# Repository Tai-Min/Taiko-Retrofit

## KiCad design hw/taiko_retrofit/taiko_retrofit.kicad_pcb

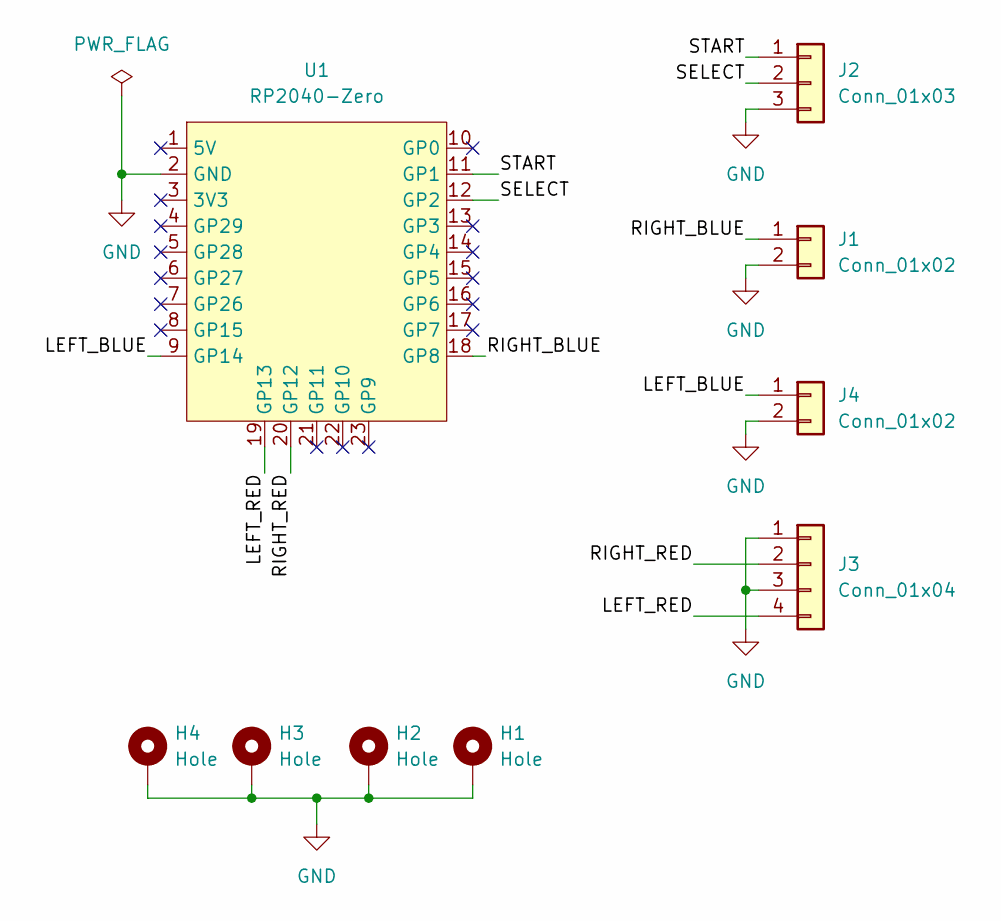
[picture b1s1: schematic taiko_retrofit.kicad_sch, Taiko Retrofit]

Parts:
H1, H2, H3, H4: Hole; MountingHole_3.2mm_M3_Pad_Via
J1, J4: Conn_01x02; Taiko2Pins
J2: Conn_01x03; JST_XH_B3B-XH-A_1x03_P2.50mm_Vertical
J3: Conn_01x04; Taiko4Pins
U1: RP2040-Zero; RP2040 Zero

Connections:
/LEFT_BLUE: J4.1, U1.9 (GP14)
/LEFT_RED: J3.4, U1.19 (GP13)
/RIGHT_BLUE: J1.1, U1.18 (GP8)
/RIGHT_RED: J3.2, U1.20 (GP12)
/SELECT: J2.2, U1.12 (GP2)
/START: J2.1, U1.11 (GP1)
GND: H1.1, H2.1, H3.1, H4.1, J1.2, J2.3, J3.1, J3.3, J4.2, U1.2 (GND)

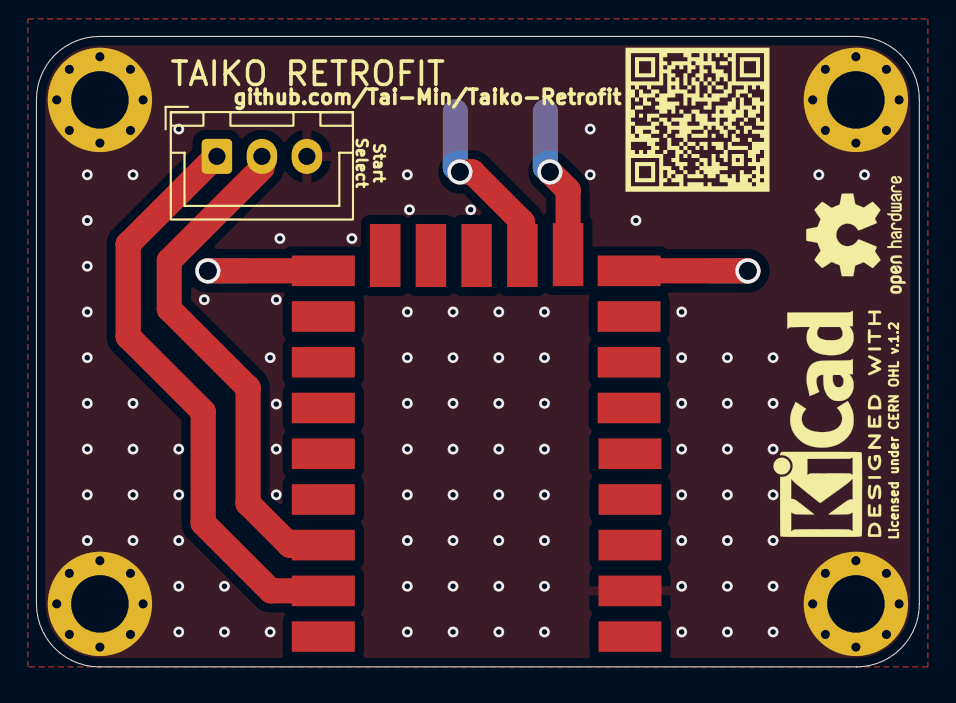
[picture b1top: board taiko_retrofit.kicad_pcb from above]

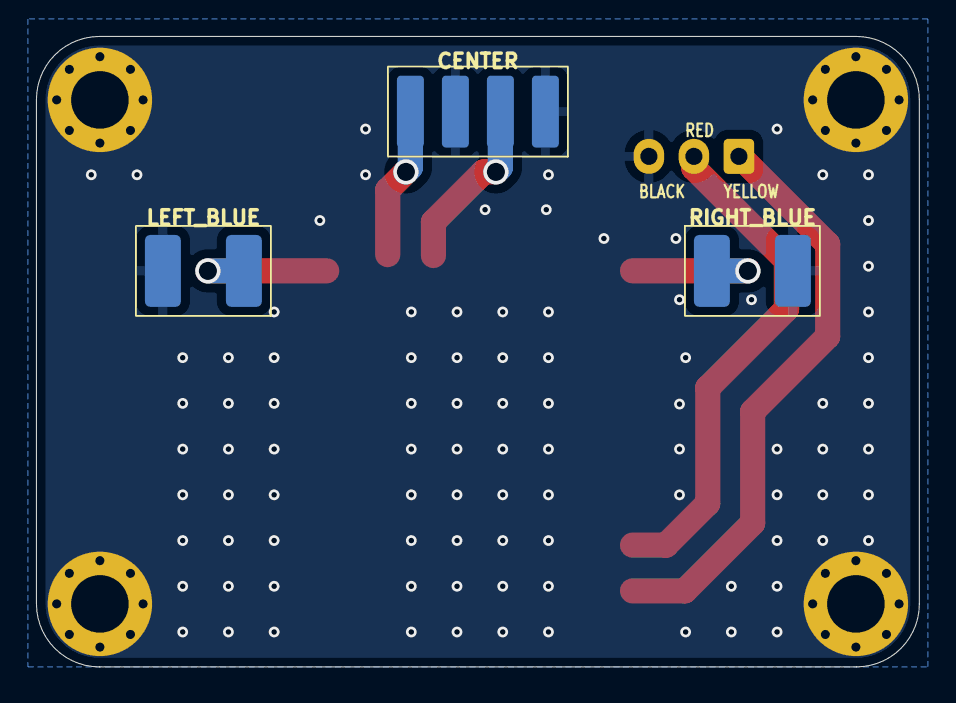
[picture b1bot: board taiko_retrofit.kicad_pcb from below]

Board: 2 copper layers, 49.1 x 35.0 mm, 9 parts (3 on the bottom side), 7 nets.

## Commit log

2026-03-09 Rename project folder
2026-03-09 Embed custom font
2026-03-23 Update PCB layout, add thanks README

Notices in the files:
hw/taiko_retrofit/taiko_retrofit.kicad_pcb:
Licensed under CERN OHL v.1.2
